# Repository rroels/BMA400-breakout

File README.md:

# Bosch BMA400 Breakout Board

> [!WARNING]
> The information and material (code, designs, files, ...) are provided "AS IS". We make no representation or warranty of any kind, express or implied, regarding the accuracy, adequacy, validity, reliability, availability, or completeness of any information or material. Use this at your own risk.

> [!WARNING]
> At the time of writing this PCB has not even been produced yet, and as such, it has not even been tested yet! Once it has been properly tested, I will confirm that everything works as expected.

## Introduction

This is a breakout board for the Bosch BMA400 acceleration sensor.

[https://www.bosch-sensortec.com/products/motion-sensors/accelerometers/bma400/](https://www.bosch-sensortec.com/products/motion-sensors/accelerometers/bma400/)

## Change Log

* v1.1
  * Modified BMA400 footprint for easier soldering by hand

* v1.0
  * Initial design 

## Design Considerations

* we chose for I2C connectivity, instead of SPI (chip supports both)
* VDD = VDDIO = 3.3V

## Schematics 

## How to Obtain the Physical PCB

The Gerber file is in this repository (`gerbers/BMA400-breakout.zip`). Simply upload this file a PCB manufacturer of your choice (JLPCB, PCBWay, ...), and you they will make it for you for as low as \$5 for 5 pieces (with the cheapest shipping option, which can take a few weeks).

For JLCPCB, select the order number option where they will replace "JLCJLCJLCJLC" on the board with the actual order number.

> [!WARNING]
> Note that will still have to solder the components onto the PCB yourself!

## How to Edit Design

Everything you need to edit this design in KiCad 8 is included in the repository.

However, this project uses symbols, footprints and 3D models from [Component Search Engine](https://componentsearchengine.com/). Their license allows us to do pretty much whatever we want with them, except redistributing them. For this reason I can't include them in this repository.

If you would like to edit the design yourself, you will need to download the following component libraries from [https://componentsearchengine.com/](https://componentsearchengine.com/) (it's free!):

* [https://componentsearchengine.com/part-view/BMA400/BOSCH](https://componentsearchengine.com/part-view/BMA400/BOSCH)

From the downloaded zip files, move the content of the `KiCad` and `3D` subfolders into the project structure, so that the end-result looks like this:

The KiCad project is configured to look for these files in these locations, using relative paths, so no changes to the project itself are required.	

## Sources

* [https://www.bosch-sensortec.com/products/motion-sensors/accelerometers/bma400/](https://www.bosch-sensortec.com/products/motion-sensors/accelerometers/bma400/)

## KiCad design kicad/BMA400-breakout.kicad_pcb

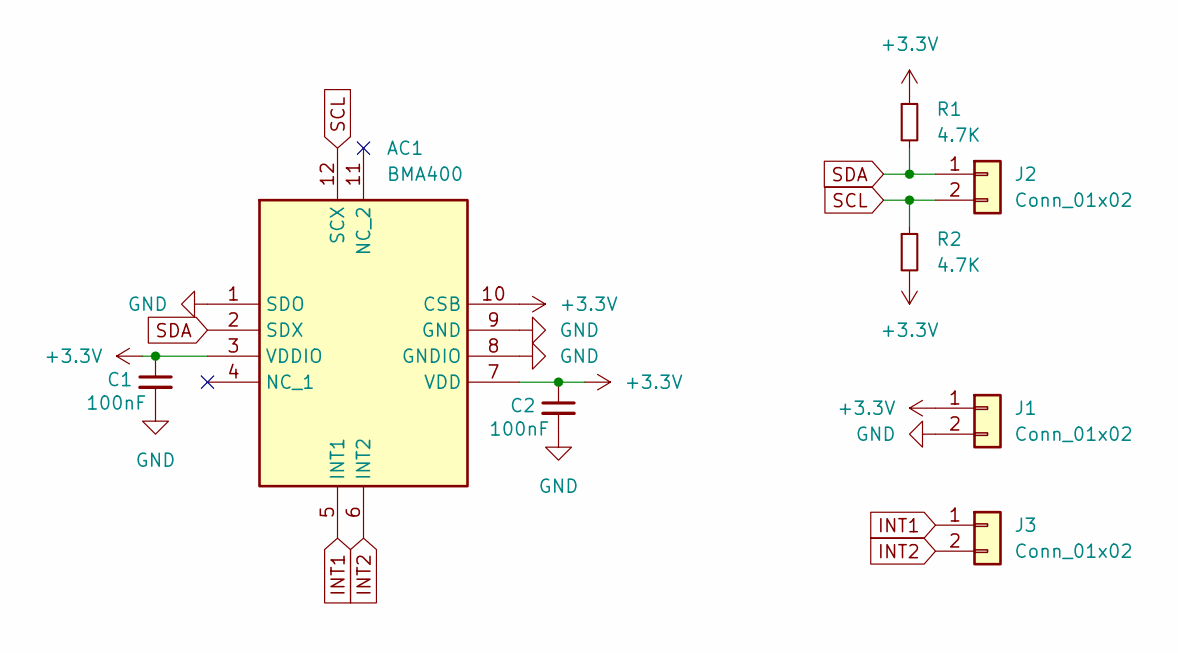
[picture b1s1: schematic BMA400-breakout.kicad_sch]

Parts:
AC1: BMA400; BOSCH_LGA-12; Manufacturer_Part_Number BMA400; Mouser Part Number 262-BMA400
C1, C2: 100nF; C_0603_1608Metric_Pad1.08x0.95mm_HandSolder
J1, J2, J3: Conn_01x02; PinHeader_1x02_P2.54mm_Vertical
R1, R2: 4.7K; R_0603_1608Metric_Pad0.98x0.95mm_HandSolder

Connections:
+3.3V: AC1.3 (VDDIO), AC1.7 (VDD), AC1.10 (CSB), C1.1, C2.1, J1.1, R1.1, R2.2
GND: AC1.1 (SDO), AC1.8 (GNDIO), AC1.9 (GND), C1.2, C2.2, J1.2
INT1: AC1.5 (INT1), J3.1
INT2: AC1.6 (INT2), J3.2
SCL: AC1.12 (SCX), J2.2, R2.1
SDA: AC1.2 (SDX), J2.1, R1.2

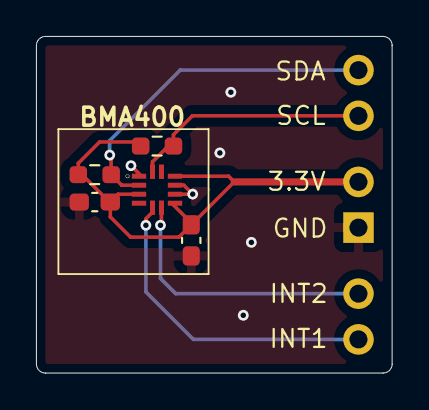
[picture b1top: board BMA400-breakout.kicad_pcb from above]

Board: 2 copper layers, 19.8 x 18.7 mm, 8 parts (0 on the bottom side), 6 nets.

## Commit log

2024-10-06 updated BMA400 footprint for easier soldering by hand
